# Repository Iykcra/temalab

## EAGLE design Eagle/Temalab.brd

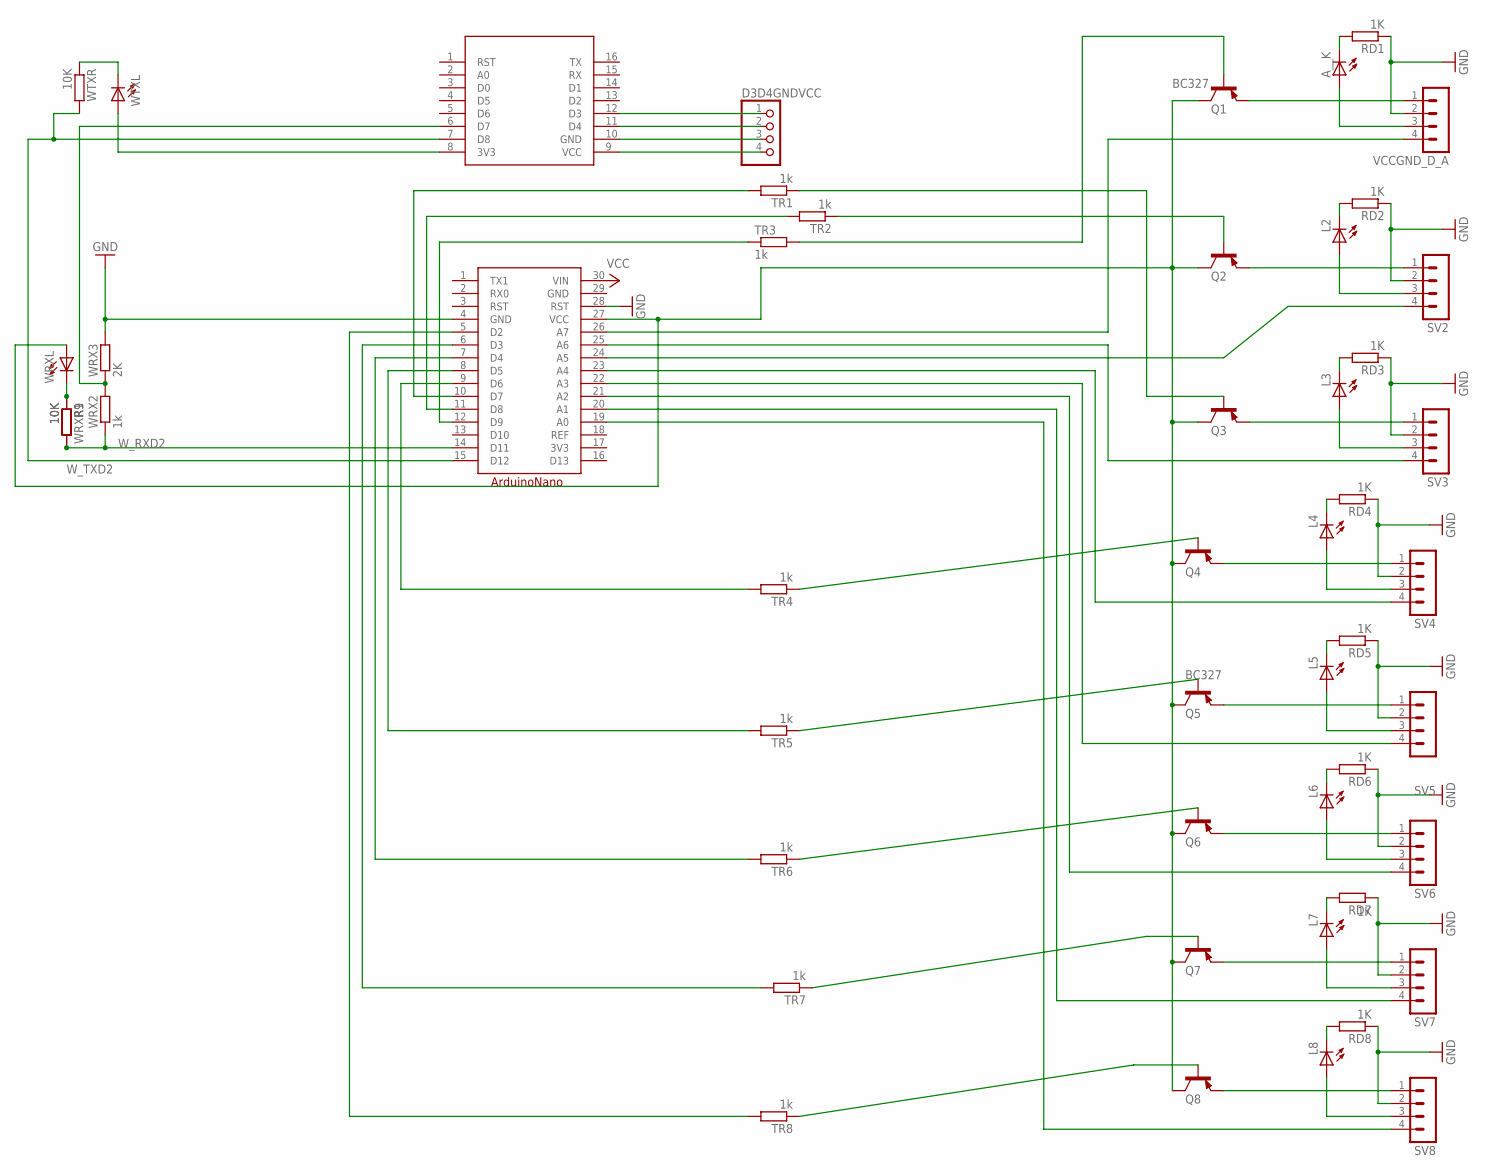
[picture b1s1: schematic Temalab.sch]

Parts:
A1: ARDUINONANO
A__K: TLLR4400; LED3MM
D3D4GNDVCC: PINHD-1X4; 1X04
L2, L3, L4, L5, L6, L7, L8: TLLR4400; LED3MM
Q1, Q2, Q3, Q4, Q5, Q6, Q7, Q8: BC327; TO92
R9: 10K; 0204V
RD1, RD2, RD3, RD4, RD5, RD6, RD7, RD8: 1K; 0204V
SV2, SV3, SV4, SV5, SV6, SV7, SV8: MA04-1
TR1, TR2, TR3, TR4, TR5, TR6, TR7, TR8: 1k; 0204/5
U$2: ESP8266MINI
VCCGND_D_A: MA04-1
WRX2: 1k; 0204/5
WRX3: 2K; 0204/5
WRXL: TLLR4400; LED3MM
WRXR1: 10K; 0204V
WTXL: A__K; LED3MM
WTXR: 10K; 0204V

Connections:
3V3: A1.17 (3V3)
GND: A1.4 (GND), A1.28 (RST), A1.29 (GND), D3D4GNDVCC.3, RD1.1, RD2.1, RD3.1, RD4.1, RD5.1, RD6.1, RD7.1, RD8.1, SV2.2, SV3.2, SV4.2, SV5.2, SV6.2, SV7.2, SV8.2, U$2.10 (GND), VCCGND_D_A.2, WRX3.2
unnamed: Q1.1 (E), VCCGND_D_A.1
unnamed: Q2.1 (E), SV2.1
unnamed: Q3.1 (E), SV3.1
unnamed: A1.12 (D9), TR3.1
unnamed: Q2.2 (B), TR2.1
unnamed: Q3.2 (B), TR1.1
unnamed: A1.26 (A7), VCCGND_D_A.4
unnamed: A1.24 (A5), SV2.4
unnamed: A1.25 (A6), SV3.4
unnamed: A1.27 (VCC), Q1.3 (C), Q2.3 (C), Q3.3 (C), Q4.3 (C), Q5.3 (C), Q6.3 (C), Q7.3 (C), Q8.3 (C), WRXL.A
unnamed: Q1.2 (B), TR3.2
unnamed: L2.A, SV2.3
unnamed: L2.K (C), RD2.2
unnamed: R9.1, WRXL.K (C), WRXR1.1
unnamed: Q4.2 (B), TR4.1
unnamed: U$2.8 (3V3), WTXL.A
unnamed: A1.11 (D8), TR2.2
unnamed: WTXL.K (C), WTXR.1
unnamed: L3.A, SV3.3
unnamed: L3.K (C), RD3.2
unnamed: U$2.6 (D7), WRX2.2, WRX3.1
unnamed: A__K.A, VCCGND_D_A.3
unnamed: A__K.K (C), RD1.2
unnamed: D3D4GNDVCC.1, U$2.12 (D3)
unnamed: D3D4GNDVCC.2, U$2.11 (D4)
unnamed: Q4.1 (E), SV4.1
unnamed: Q5.1 (E), SV5.1
unnamed: A1.19 (A0), SV8.4
unnamed: A1.20 (A1), SV7.4
unnamed: L7.A, SV7.3
unnamed: L8.A, SV8.3
unnamed: L8.K (C), RD8.2
unnamed: Q6.1 (E), SV6.1
unnamed: L7.K (C), RD7.2
unnamed: Q7.1 (E), SV7.1
unnamed: Q8.1 (E), SV8.1
unnamed: A1.21 (A2), SV6.4
unnamed: L6.A, SV6.3
unnamed: L6.K (C), RD6.2
unnamed: A1.9 (D6), TR4.2
unnamed: L5.A, SV5.3
unnamed: L5.K (C), RD5.2
unnamed: A1.23 (A4), SV4.4
unnamed: L4.A, SV4.3
unnamed: L4.K (C), RD4.2
unnamed: A1.8 (D5), TR5.2
unnamed: A1.22 (A3), SV5.4
unnamed: A1.7 (D4), TR6.2
unnamed: A1.6 (D3), TR7.2
unnamed: A1.5 (D2), TR8.2
unnamed: A1.10 (D7), TR1.2
unnamed: Q5.2 (B), TR5.1
unnamed: Q6.2 (B), TR6.1
unnamed: Q7.2 (B), TR7.1
unnamed: Q8.2 (B), TR8.1
REF: A1.18 (REF)
VCC: A1.30 (VIN), D3D4GNDVCC.4, U$2.9 (VCC)
W_RXD2: A1.14 (D11), R9.2, WRX2.1, WRXR1.2
W_TXD2: A1.15 (D12), U$2.7 (D8), WTXR.2

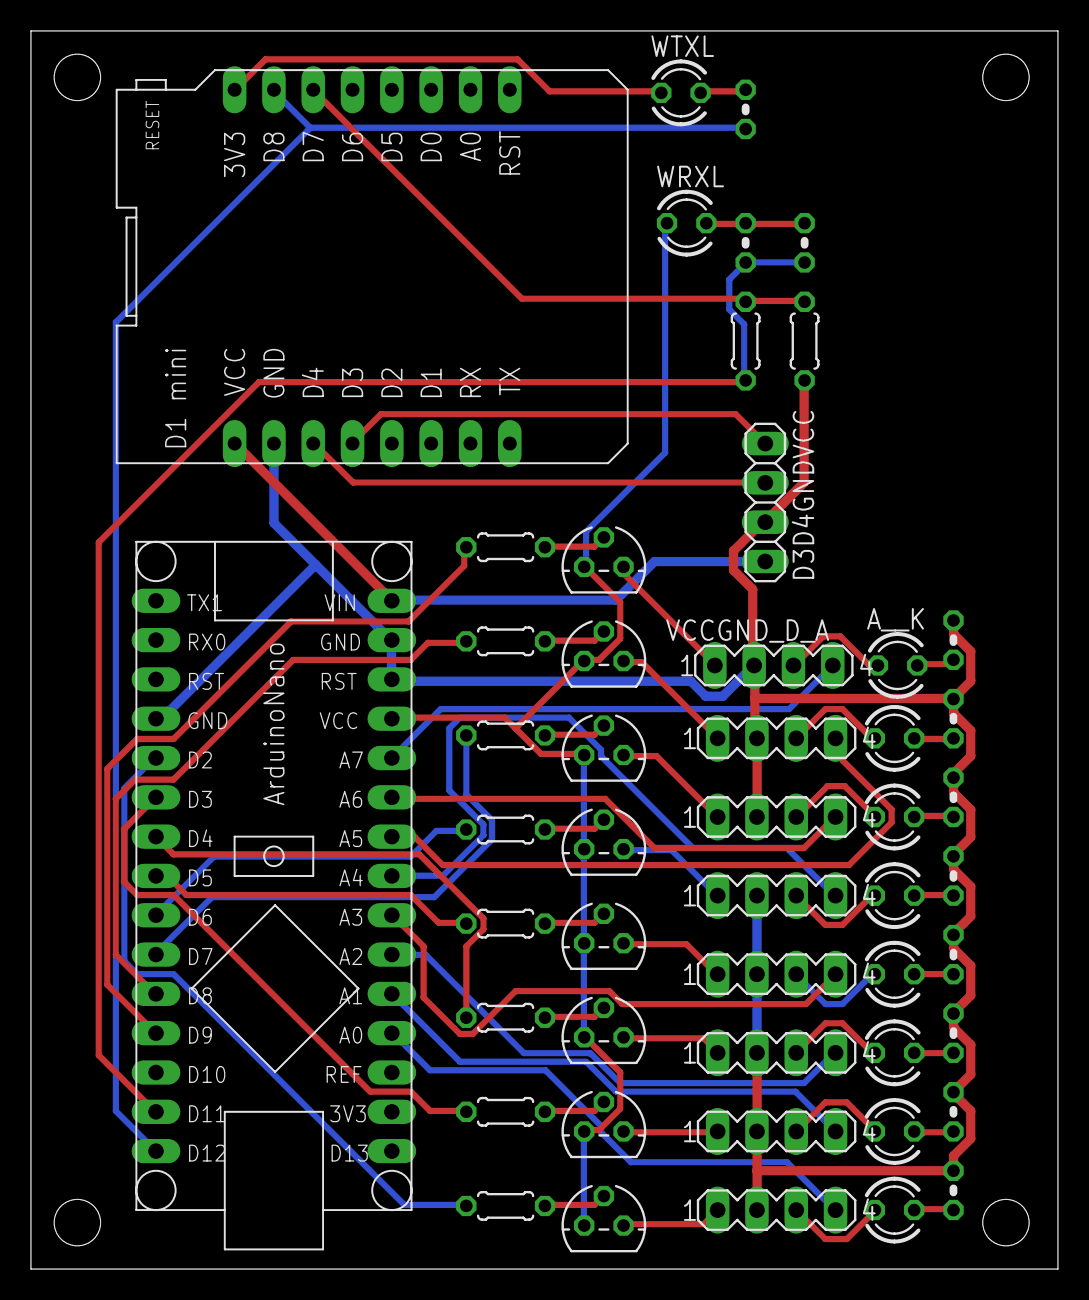
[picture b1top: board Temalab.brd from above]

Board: 2 copper layers, 66.4 x 80.0 mm, 50 parts (0 on the bottom side), 59 nets.

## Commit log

2018-12-10 Create Temalab.ino
    Arduino File (1 db)
    Eagle File (34 db)
2019-03-12 datafolder+nanoscketch
    rwgsfgsfgsdgdsd
